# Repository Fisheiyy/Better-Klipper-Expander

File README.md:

# THIS PROJECT HAS BEEN ABANDONED

# Better Klipper Expander
 A RP2040 based 3D Printer Port Expander with 6 Fan Ports, Selectable Fan Voltage (24V/5V) (3 Fans per Voltage Selection Header), 2 Thermistor ports (1 with PT1000 Support), and a Positive Driven Fan Port (FAN5) for CPAP Fan Drivers.

## [iBOM](https://htmlpreview.github.io/?https://github.com/Fisheiyy/Better-Klipper-Expander/blob/main/ibom.html), [BOM](https://docs.google.com/spreadsheets/d/1mPUtkNYWScB2l85k0YQtJtEaqjWuknqn7hNMz57VFFw/edit#gid=1487594272), [Schematic](https://github.com/Fisheiyy/Better-Klipper-Expander/blob/main/better-klipper-expander.pdf) <br><br> Inspired by [Klipper Expander](https://github.com/timmit99/Klipper-Expander) by [timmit99](https://github.com/timmit99) <br> Made for the Voron & Klipper Communities
<hr>

# PICTURES
 ### V1 Picture
 
<hr>

# LICENSE
 #### **You CANNOT use anything in this repo for Commercial Use without EXPLICIT PERMISSION**
*You can contact me if you have any questions regarding this.*
 ## This repository is under the [CC-BY-NC-SA-4.0](https://creativecommons.org/licenses/by-nc-sa/4.0) which states:
 ### You are free to:
   - Share — copy and redistribute the material in any medium or format
   - Adapt — remix, transform, and build upon the material
 ### Under the following terms:
  - Attribution — You **must** give **appropriate credit**, **provide a link to the license**, and **indicate if changes were made**. You may do so in any reasonable manner, but not in any way that suggests the licensor endorses you or your use.
  - NonCommercial — You may **not** use the material for **commercial purposes.**
  - ShareAlike — If you remix, transform, or build upon the material, you **must distribute your contributions under the same license as the original.**

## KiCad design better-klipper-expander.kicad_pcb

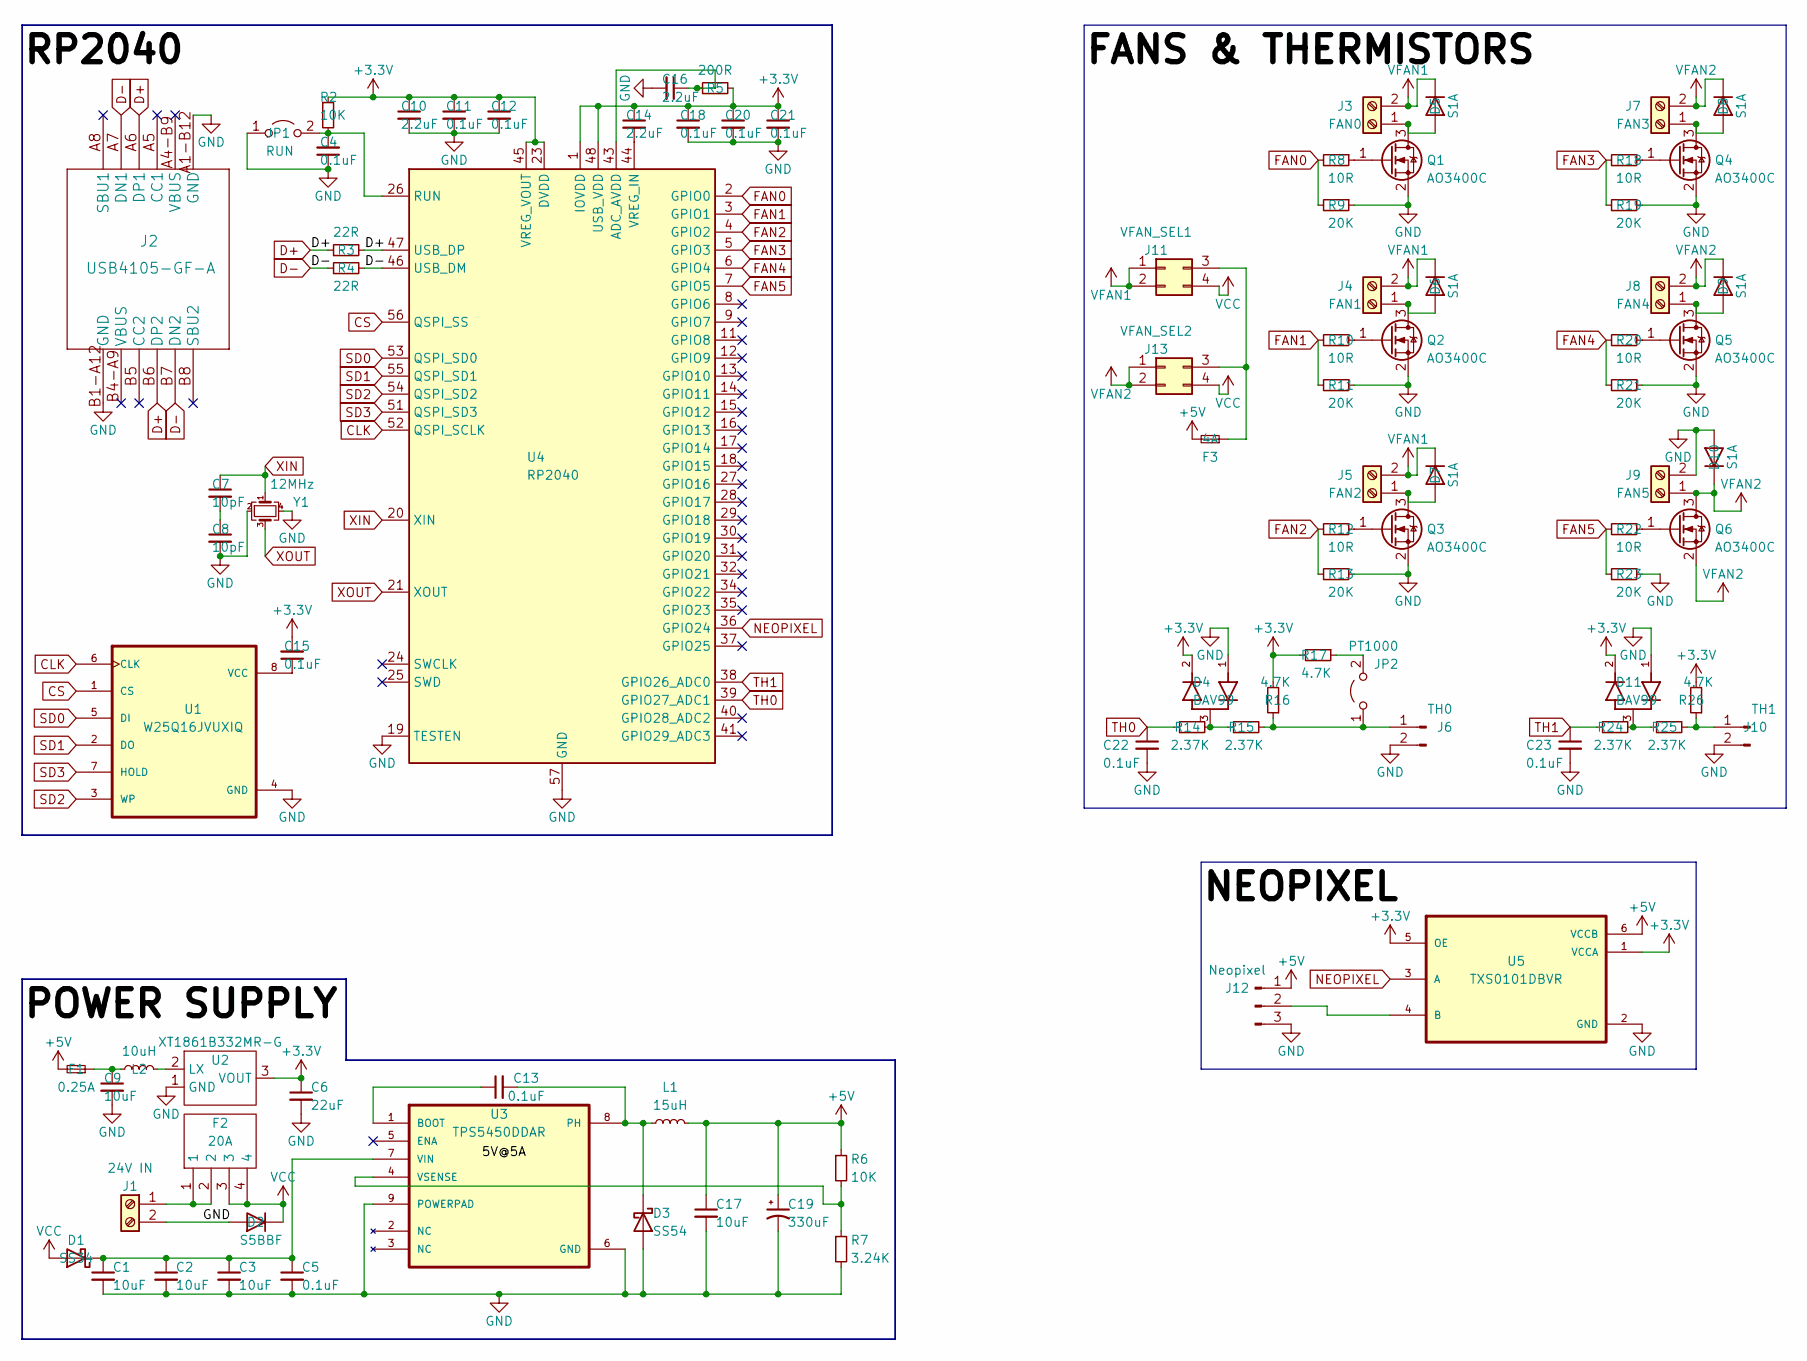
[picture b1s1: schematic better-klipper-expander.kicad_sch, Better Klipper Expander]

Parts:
C1, C2, C3, C9, C17: 10uF; C_0805_2012Metric
C4, C5, C11, C12, C13, C15, C18, C20, C21, C22, C23: 0.1uF; C_0805_2012Metric
C6: 22uF; C_0805_2012Metric
C7, C8: 10pF; C_0603_1608Metric
C10, C14, C16: 2.2uF; C_0805_2012Metric
C19: 330uF; CP_Radial_D8.0mm_P3.50mm
D1: SS34; D_SMA
D2: S5BBF; D_SMB_Handsoldering
D3: SS54; D_SMA
D4, D11: BAV99; DIO_BAV99
D5, D6, D7, D8, D9, D10: S1A; D_SMA
F1: 0.25A; Fuse_0603_1608Metric_Pad1.05x0.95mm_HandSolder
F2: 20A; 01000063Z
F3: 4A; Fuse_0805_2012Metric
J1: 24V IN; TerminalBlock_Phoenix_MKDS-1,5-2_1x02_P5.00mm_Horizontal
J2: USB4105-GF-A
J3: FAN0; JST_XH_B2B-XH-A_1x02_P2.50mm_Vertical
J4: FAN1; JST_XH_B2B-XH-A_1x02_P2.50mm_Vertical
J5: FAN2; JST_XH_B2B-XH-A_1x02_P2.50mm_Vertical
J6: TH0; JST_XH_B2B-XH-A_1x02_P2.50mm_Vertical
J7: FAN3; JST_XH_B2B-XH-A_1x02_P2.50mm_Vertical
J8: FAN4; JST_XH_B2B-XH-A_1x02_P2.50mm_Vertical
J9: FAN5; JST_XH_B2B-XH-A_1x02_P2.50mm_Vertical
J10: TH1; JST_XH_B2B-XH-A_1x02_P2.50mm_Vertical
J11: VFAN_SEL1; PinHeader_2x02_P2.54mm_Vertical
J12: Neopixel; PinHeader_1x03_P2.54mm_Vertical
J13: VFAN_SEL2; PinHeader_2x02_P2.54mm_Vertical
JP1: RUN; PinHeader_1x02_P2.54mm_Vertical
JP2: PT1000; PinHeader_1x02_P2.54mm_Vertical
L1: 15uH; L_1210_3225Metric
L2: 10uH; Fuse_0805_2012Metric
Q1, Q2, Q3, Q4, Q5, Q6: AO3400C; SOT-23
R2, R6: 10K; R_0805_2012Metric
R3, R4: 22R; R_0805_2012Metric
R5: 200R; R_0805_2012Metric
R7: 3.24K; R_0805_2012Metric
R8, R10, R12, R18, R20, R22: 10R; R_0805_2012Metric
R9, R11, R13, R19, R21, R23: 20K; R_0805_2012Metric
R14, R15, R24, R25: 2.37K; R_0805_2012Metric
R16, R17, R26: 4.7K; R_0805_2012Metric
U1: W25Q16JVUXIQ; SON50P300X200X60-9N
U2: XT1861B332MR-G; SOT-23
U3: TPS5450DDAR; VREG_LM5017MR/NOPB
U4: RP2040; QFN-56-1EP_7x7mm_P0.4mm_EP3.2x3.2mm
U5: TXS0101DBVR; SOT95P280X145-6N
Y1: 12MHz; Oscillator_SMD_SeikoEpson_SG8002CE-4Pin_3.2x2.5mm

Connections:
+3.3V: C6.1, C10.1, C11.1, C12.1, C14.1, C15.2, C18.1, C20.1, C21.1, D4.2, D11.2, R2.1, R5.2, R16.2, R17.2, R26.2, U2.3 (VOUT), U4.1 (IOVDD), U4.10 (IOVDD), U4.22 (IOVDD), U4.23 (DVDD), U4.33 (IOVDD), U4.42 (IOVDD), U4.45 (VREG_VOUT), U4.48 (USB_VDD), U4.49 (IOVDD), U4.50 (DVDD), U5.1 (VCCA), U5.5 (OE)
+5V: C17.1, C19.1, F1.2, F3.2, J12.1, L1.2, R6.1, U5.6 (VCCB)
CLK: U1.6 (CLK), U4.52 (QSPI_SCLK)
CS: U1.1 (CS), U4.56 (QSPI_SS)
D+: J2.A6 (DP1), J2.B6 (DP2), R3.1, R3.2, U4.47 (USB_DP)
D-: J2.A7 (DN1), J2.B7 (DN2), R4.1, R4.2, U4.46 (USB_DM)
FAN0: R8.2, R9.2, U4.2 (GPIO0)
FAN1: R10.2, R11.2, U4.3 (GPIO1)
FAN2: R12.2, R13.2, U4.4 (GPIO2)
FAN3: R18.2, R19.2, U4.5 (GPIO3)
FAN4: R20.2, R21.2, U4.6 (GPIO4)
FAN5: R22.2, R23.2, U4.7 (GPIO5)
GND: C1.2, C2.2, C3.2, C4.1, C5.2, C6.2, C8.2, C9.2, C10.2, C11.2, C12.2, C16.2, C17.2, C18.2, C19.2, C20.2, C21.2, C22.2, C23.2, D2.1 (A), D3.2 (A), D4.1, D10.2 (A), D11.1, J1.2, J2.A1-B12 (GND), J2.B1-A12 (GND), J6.2, J9.2, J10.2, J12.3, JP1.1 (A), Q1.2 (S), Q2.2 (S), Q3.2 (S), Q4.2 (S), Q5.2 (S), R7.2, R9.1, R11.1, R13.1, R19.1, R21.1, R23.1, U1.4 (GND), U2.1 (GND), U3.6 (GND), U3.9 (POWERPAD), U4.19 (TESTEN), U4.57 (GND), U5.2 (GND), Y1.2, Y1.4
NEOPIXEL: U4.36 (GPIO24), U5.3 (A)
unnamed: C1.1, C2.1, C3.1, C5.1, D1.1 (K), U3.7 (VIN)
unnamed: C4.2, JP1.2 (B), R2.2, U4.26 (RUN)
unnamed: C7.2, C8.1
unnamed: C9.1, F1.1, L2.1
unnamed: C13.1, U3.1 (BOOT)
unnamed: C13.2, D3.1 (K), L1.1, U3.8 (PH)
unnamed: C14.2, U4.44 (VREG_IN)
unnamed: C15.1, U1.8 (VCC)
unnamed: C16.1, R5.1, U4.43 (ADC_AVDD)
unnamed: D4.3, R14.2, R15.1
unnamed: D5.2 (A), J3.1, Q1.3 (D)
unnamed: D6.2 (A), J4.1, Q2.3 (D)
unnamed: D7.2 (A), J5.1, Q3.3 (D)
unnamed: D8.2 (A), J7.1, Q4.3 (D)
unnamed: D9.2 (A), J8.1, Q5.3 (D)
unnamed: D11.3, R24.2, R25.1
unnamed: F2.1, F2.2, J1.1
unnamed: F3.1, J11.3, J13.3
unnamed: J6.1, JP2.1 (A), R15.2, R16.1
unnamed: J10.1, R25.2, R26.1
unnamed: J12.2, U5.4 (B)
unnamed: JP2.2 (B), R17.1
unnamed: L2.2, U2.2 (LX)
unnamed: Q1.1 (G), R8.1
unnamed: Q2.1 (G), R10.1
unnamed: Q3.1 (G), R12.1
unnamed: Q4.1 (G), R18.1
unnamed: Q5.1 (G), R20.1
unnamed: Q6.1 (G), R22.1
unnamed: R6.2, R7.1, U3.4 (VSENSE)
SD0: U1.5 (DI), U4.53 (QSPI_SD0)
SD1: U1.2 (DO), U4.55 (QSPI_SD1)
SD2: U1.3 (WP), U4.54 (QSPI_SD2)
SD3: U1.7 (HOLD), U4.51 (QSPI_SD3)
TH0: C22.1, R14.1, U4.39 (GPIO27_ADC1)
TH1: C23.1, R24.1, U4.38 (GPIO26_ADC0)
VCC: D1.2 (A), D2.2 (K), F2.3, F2.4, J11.4, J13.4
XIN: C7.1, U4.20 (XIN), Y1.1
XOUT: U4.21 (XOUT), Y1.3

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
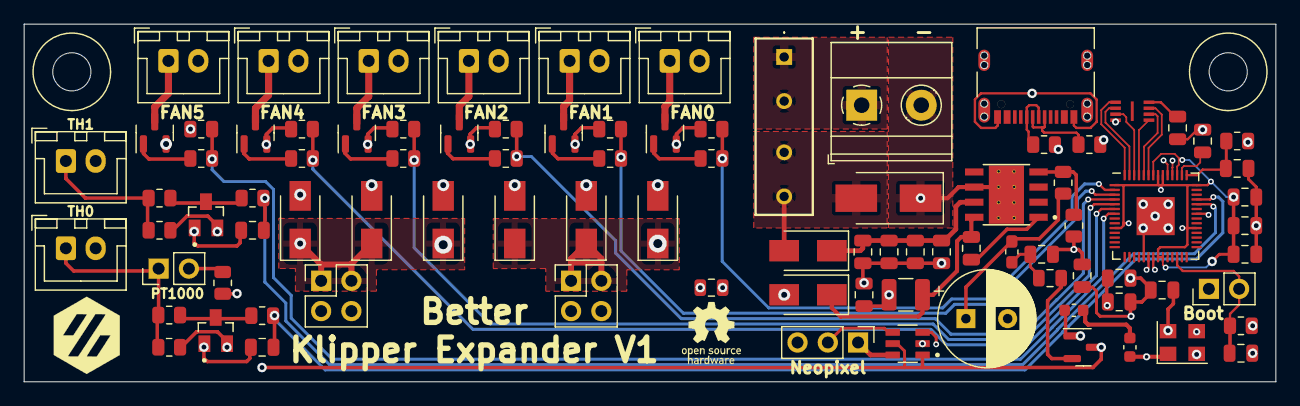
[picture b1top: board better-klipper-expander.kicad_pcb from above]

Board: 4 copper layers, 105.0 x 30.0 mm, 93 parts (0 on the bottom side), 54 nets.

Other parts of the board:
H1, H2: MountingHole; MountingHole_3.2mm_M3

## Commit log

2022-10-04 init
2022-10-06 Finished V1
2022-10-08 Vias, Widths, and Organization...
2022-10-10 Neopixelssssss....
2022-10-10 3 fans per voltage selection now
2022-10-11 remove silkscreen things i forgot
2022-11-19 Minor updates
2022-12-20 change flash + fix major problem + minor cleanup
2022-12-25 Update Readme + Re-export Gerbers + Pics
2022-12-25 Move Flash Closer to RP2040

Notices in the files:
parts and their libraries:
Copyright 2021 Accelerated Designs. All rights reserved.
